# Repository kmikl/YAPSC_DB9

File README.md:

# YAPSCO_DB9
Fork of YASPCO-10V with following changes:
- Removed 15 Pin connector
- Changed pinout of the feedback connector to directly connect the cheap linear scales
- Replaced jumper headers to solder headers
- Routing cleanup
- Jumper from pin 4 to 5V for the optional 1um resolution of some scales

## Specifications
* Input voltage +12V..+24V
* Same as YAPSC:10V

## Board Status:
- Tested, working

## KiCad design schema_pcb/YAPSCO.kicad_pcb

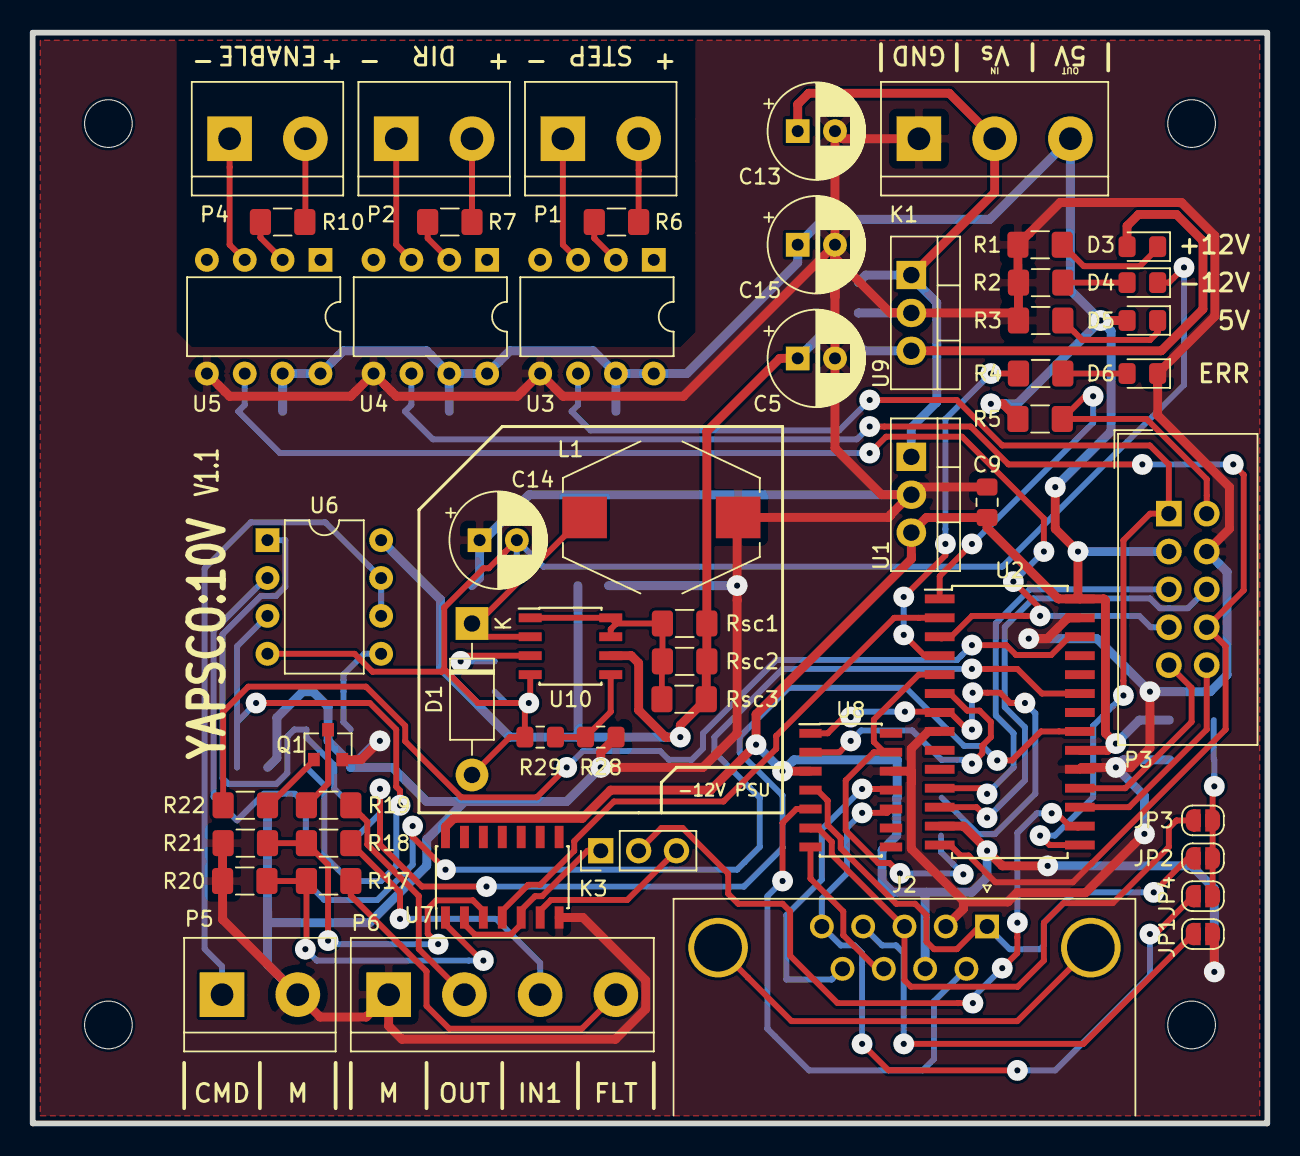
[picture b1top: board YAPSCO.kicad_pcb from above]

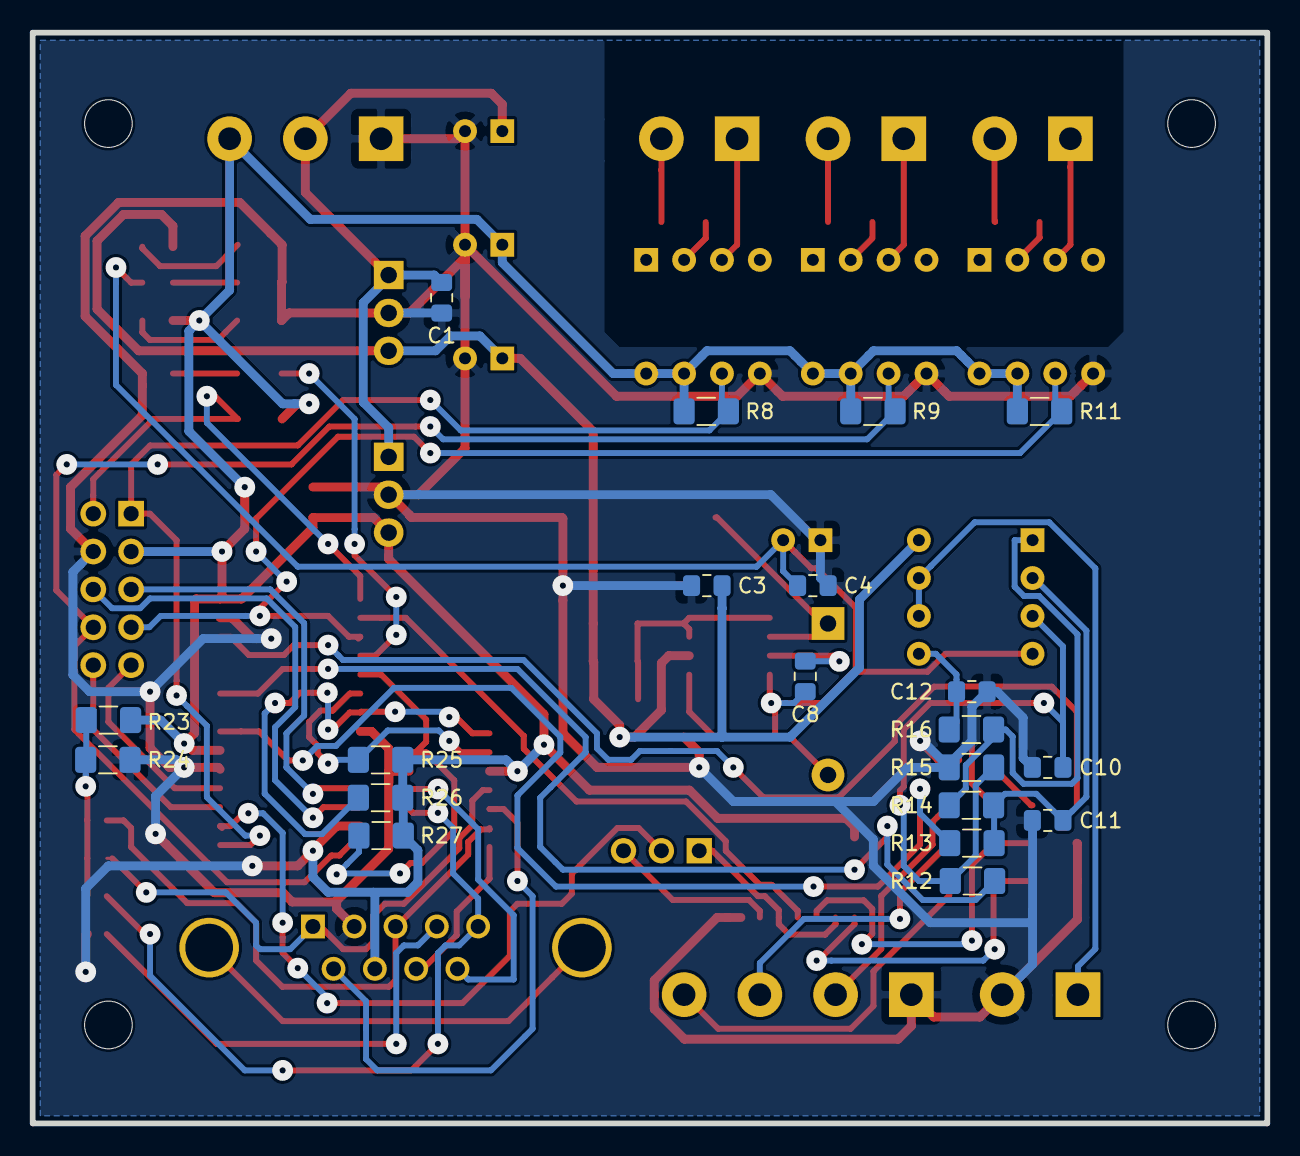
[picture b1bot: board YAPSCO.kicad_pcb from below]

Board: 2 copper layers, 82.8 x 73.2 mm, 78 parts (20 on the bottom side), 61 nets.

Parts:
C1, C3, C4, C9: 100nF; C_0805_2012Metric_Pad1.15x1.40mm_HandSolder
C5, C13, C15: 100uF; CP_Radial_D6.3mm_P2.50mm
C8: 360p; C_0805_2012Metric_Pad1.15x1.40mm_HandSolder
C10, C11, C12: 33nF; C_0805_2012Metric_Pad1.15x1.40mm_HandSolder
C14: 100u; CP_Radial_D6.3mm_P2.50mm
D1: 1N5819; D_DO-41_SOD81_P10.16mm_Horizontal
D3: +12; D_0805_2012Metric_Pad1.15x1.40mm_HandSolder
D4: -12; D_0805_2012Metric_Pad1.15x1.40mm_HandSolder
D5: LED 5V; LED_0805_2012Metric_Pad1.15x1.40mm_HandSolder
D6: LED; LED_0805_2012Metric_Pad1.15x1.40mm_HandSolder
H1, H2, H3, H4: MountingHole; MountingHole_3.2mm_M3_ISO7380
J2: DB9_Female_MountingHoles; DSUB-9_Female_Horizontal_P2.77x2.84mm_EdgePinOffset9.90mm_H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
JP1, JP2, JP3, JP4: SolderJumper_2_Open; SolderJumper-2_P1.3mm_Open_RoundedPad1.0x1.5mm
K1: Supply; TerminalBlock_bornier-3_P5.08mm
K3: FautlPol; PinHeader_1x03_P2.54mm_Vertical
L1: 1m; L_Bourns-SRR1005
P1: STEP; TerminalBlock_bornier-2_P5.08mm
P2: DIR; TerminalBlock_bornier-2_P5.08mm
P3: CONN; IDC-Header_2x05_P2.54mm_Vertical
P4: ENABLE; TerminalBlock_bornier-2_P5.08mm
P5: +-10V; TerminalBlock_bornier-2_P5.08mm
P6: InOut; TerminalBlock_bornier-4_P5.08mm
Q1: NPN; SOT-23
R1, R2: 2K2; R_1206_3216Metric_Pad1.42x1.75mm_HandSolder
R3, R4, R6, R7, R10: 470; R_1206_3216Metric_Pad1.42x1.75mm_HandSolder
R5: 10K; R_1206_3216Metric_Pad1.42x1.75mm_HandSolder
R8, R9, R11, R25, R26, R27: 4K7; R_1206_3216Metric_Pad1.42x1.75mm_HandSolder
R12, R13: 22K; R_1206_3216Metric_Pad1.42x1.75mm_HandSolder
R14, R15: 47K; R_1206_3216Metric_Pad1.42x1.75mm_HandSolder
R16: 22k; R_1206_3216Metric_Pad1.42x1.75mm_HandSolder
R17, R18, R20, R21: R; R_1206_3216Metric_Pad1.42x1.75mm_HandSolder
R19: 100; R_1206_3216Metric_Pad1.42x1.75mm_HandSolder
R22, R23, R24: 1K; R_1206_3216Metric_Pad1.42x1.75mm_HandSolder
R28: 8K6; R_0805_2012Metric_Pad1.15x1.40mm_HandSolder
R29: 1K; R_0805_2012Metric_Pad1.15x1.40mm_HandSolder
Rsc1, Rsc2, Rsc3: 1R; R_1206_3216Metric_Pad1.42x1.75mm_HandSolder
U1: 7805; TO-220-3_Vertical
U2: dsPIC30F4012; SOIC-28W_7.5x17.9mm_P1.27mm
U3, U4, U5: 6N137; DIP-8_W7.62mm
U6: LM358; DIP-8_W7.62mm
U7: 74HC14; SOIC-14_3.9x8.7mm_P1.27mm
U8: LM339D; SOIC-14_3.9x8.7mm_P1.27mm
U9: L7812; TO-220-3_Vertical
U10: MC33063AD; SOIC-8_3.9x4.9mm_P1.27mm

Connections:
+2V5: JP2.2, JP3.2, JP4.2, R23.2, R24.1
+5V: C9.1, C15.1, D5.2, J2.7, JP1.2, K1.3, P3.3, R5.1, R8.1, R9.1, R11.1, R23.1, R25.1, R26.1, R27.1, U1.3, U2.13, U2.20, U2.28, U3.7, U3.8, U4.7, U4.8, U5.7, U5.8, U7.14, U8.3
+12V: C3.1, C5.1, D3.2, Rsc1.2, Rsc2.2, Rsc3.2, U6.8, U9.3, U10.6
-12V: C4.2, C8.2, C14.2, D1.2, D4.1, R29.2, U6.4, U10.4
/Encoder/A+: J2.6, U8.5
/Encoder/A-: J2.1, JP2.1, U8.4
/Encoder/B+: J2.8, U8.7
/Encoder/B-: J2.3, JP3.1, U8.6
/Encoder/I+: J2.9, U8.11
/Encoder/I-: J2.5, JP4.1, U8.10
/Encoder/INDX: R27.2, U2.5, U8.13
/Encoder/QEA: R25.2, U2.6, U8.2
/Encoder/QEB: R26.2, U2.7, U8.1
/InterfaceDriver/FLTA: K3.2, U2.16
/InterfaceDriver/IN1: U2.2, U7.4
/InterfaceDriver/Neg: R13.2, U2.21
/InterfaceDriver/OUT1: R22.1, U2.26
/MotionControllerInput/DIR: P3.8, R9.2, U2.14, U4.6
/MotionControllerInput/ENABLE: P3.7, R11.2, U2.3, U5.6
/MotionControllerInput/MCLR: P3.2, R5.2, U2.1
/MotionControllerInput/PGC: P3.9, U2.18
/MotionControllerInput/PGD: P3.10, U2.17
/MotionControllerInput/STEP: P3.1, R8.2, U2.15, U3.6
/SupplyCircuit/InputVoltageRail: C1.1, C13.1, K1.2, U1.1, U9.1
/dsPIC/PWM_H_A: R12.2, U2.23
/dsPIC/RX: P3.6, U2.12
/dsPIC/TX: P3.5, U2.11
GND: C1.2, C3.2, C4.1, C5.2, C9.2, C10.1, C11.2, C12.2, C13.2, C14.1, C15.2, D6.1, J2.2, K1.1, L1.2, P3.4, P5.2, P6.1, Q1.2, R1.1, R2.1, R3.2, R15.1, R20.1, R21.1, R24.2, R28.2, U1.2, U2.8, U2.19, U2.27, U3.5, U4.5, U5.5, U7.7, U8.12, U9.2
unnamed: C8.1, U10.3
unnamed: C10.2, R12.1, R15.2, U6.3
unnamed: C11.1, R13.1, R14.2, U6.2
unnamed: C12.1, R16.1, U6.5
unnamed: D1.1, L1.1, U10.2
unnamed: D3.1, R1.2
unnamed: D4.2, R2.2
unnamed: D5.1, R3.1
unnamed: D6.2, R4.2
unnamed: J2.4, JP1.1
unnamed: K3.1, U7.2, U7.5
unnamed: K3.3, U7.6
unnamed: P1.1, U3.3
unnamed: P1.2, R6.2
unnamed: P2.1, U4.3
unnamed: P2.2, R7.2
unnamed: P4.1, U5.3
unnamed: P4.2, R10.2
unnamed: P5.1, U6.6, U6.7
unnamed: P6.2, R19.2
unnamed: P6.3, R18.2
unnamed: P6.4, R17.2
unnamed: Q1.1, R22.2
unnamed: Q1.3, R19.1
unnamed: R4.1, U2.4
unnamed: R6.1, U3.2
unnamed: R7.1, U4.2
unnamed: R10.1, U5.2
unnamed: R14.1, R16.2, U6.1
unnamed: R17.1, R20.2, U7.1
unnamed: R18.1, R21.2, U7.3
unnamed: R28.1, R29.1, U10.5
unnamed: Rsc1.1, Rsc2.1, Rsc3.1, U10.1, U10.7, U10.8

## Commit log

2020-09-27 Feedback changed to cheap linear scale
2020-09-27 PCB Ordered
